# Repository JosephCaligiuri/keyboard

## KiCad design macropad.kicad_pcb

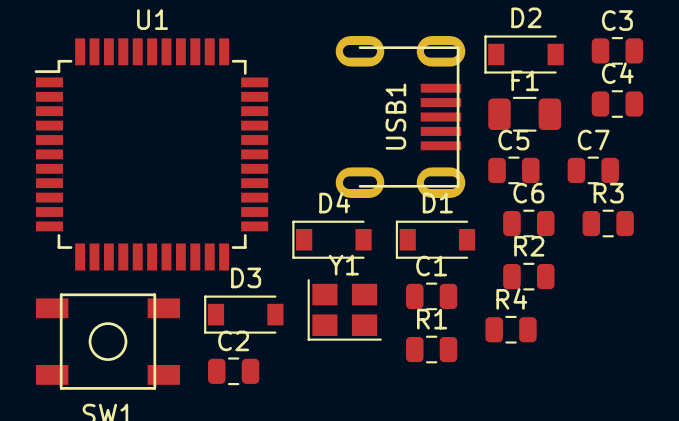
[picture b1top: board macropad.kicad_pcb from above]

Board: 2 copper layers, 20 parts (0 on the bottom side), 16 nets, no tracks yet.

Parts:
C1, C2: 22pF; C_0805_2012Metric
C3: 1uF; C_0805_2012Metric
C4, C5, C6: 0.1uF; C_0805_2012Metric
C7: 10uF; C_0805_2012Metric
D1, D2, D3, D4: D_Small; D_SOD-123
F1: 500mA; Fuse_1206_3216Metric
R1, R4: 10k; R_0805_2012Metric
R2, R3: 22; R_0805_2012Metric
SW1: SW_Push; SKQG-1155865
U1: ATmega32U4-AU; TQFP-44_10x10mm_P0.8mm
USB1: Molex-0548190589
Y1: 16MHz; Crystal_SMD_3225-4Pin_3.2x2.5mm

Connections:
+5V: C4.1, C5.1, C6.1, C7.1, F1.1, R1.2, U1.2, U1.7, U1.14, U1.34
D+: R2.2, USB1.3
D-: R3.2, USB1.4
GND: C1.2, C2.2, C3.2, C4.2, C5.2, C6.2, C7.2, R4.2, SW1.1, U1.5, USB1.1, Y1.1, Y1.3
unnamed: C1.1, U1.17, Y1.4
unnamed: C2.1, U1.16, Y1.2
unnamed: C3.1, U1.6
unnamed: R1.1, SW1.2, U1.13
unnamed: R2.1, U1.4
unnamed: R3.1, U1.3
unnamed: R4.1, U1.33
unnamed: U1.15, U1.23, U1.35, U1.43
unnamed: U1.24, U1.44
ROW0: D1.1, D2.1
ROW1: D3.1, D4.1
VCC: F1.2, USB1.5

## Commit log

2023-10-08 init project
2023-10-08 change structure
2023-10-08 Add submodules
2023-10-08 add footprint lib
2023-10-09 10/8/23
